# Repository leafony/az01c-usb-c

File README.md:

# Leafony AZ01C USB-C シリアル変換リーフ

## 概要

Leafony AZ01C は、Leafony Bus 向けの USB-C to UART リーフである。USB 接続時は FT234XD による USB-UART 変換と、USB VBUS から生成した 3.3V 電源を Leafony Bus へ供給する。

USB 未接続時に他リーフ側のバッテリーから 3.3V が供給される構成でも、UART 信号線と 3.3V 電源ラインのバックフィードを抑え、USB-C リーフ側が無駄な電力を消費しないことを設計方針とする。信号線は TS3A4741 で物理的に切断し、電源ラインは TPS6282533 出力と Leafony Bus 3.3V の間に MAX40200AUK+T 理想ダイオードを入れて逆流を遮断する。

## 主な用途

- Leafony リーフへの MCU 書き込み
- Leafony リーフの UART デバッグ
- USB から Leafony Bus への 3.3V 電源供給

## 仕様

### 電気的仕様

| 項目 | Min | Typ | Max | 単位 | 備考 |
|---|---:|---:|---:|---|---|
| USB VBUS 入力電圧 | 4.5 | 5.0 | 5.5 | V | USB-C UFP/Sink として使用 |
| Buck 出力電圧 `P3V3_BUCK` | 3.27 | 3.30 | 3.33 | V | TPS6282533 固定 3.3V、精度 ±1% |
| Leafony Bus 3.3V 出力 | - | 3.26 | - | V | MAX40200 通過後。500mA 時は約 43mV 低下 |
| Leafony Bus 3.3V 出力電流 | - | - | 500 | mA | TPS6282533 は 2A 品、MAX40200 は 1A 品。本設計では 500mA 上限 |
| MAX40200 逆方向リーク | - | 0.07 | 1.5 | µA | Leafony Bus +3.3V から `P3V3_BUCK` 方向 |
| UART 通信速度 | 300 | - | 3,000,000 | baud | FT234XD 仕様 |
| UART I/O 論理電圧 | - | 3.3 | - | V | FT234XD VCCIO を Leafony Bus 3.3V rail に接続 |
| USB 接続時アイドル消費 | - | 12 | - | mA | FT234XD、Buck、MAX40200、LED 周辺を含む概算 |
| USB 未接続時バッテリー側消費 | - | 0.15 | 2.3 | µA | MAX40200 逆方向リークと TS3A4741 待機電流のデータシート値から算出。FT234XD の VCC=0V、VCCIO=3.3V 条件は実機確認対象 |
| 動作温度範囲 | -40 | 25 | +85 | ℃ | 構成部品の最小共通範囲 |

### 機械的仕様

| 項目 | 仕様 |
|---|---|
| 外形寸法 | Leafony 20mm x 20mm |
| 基板厚 | 0.8mm 推奨 |
| 層数 | 4層 |
| 実装 | 両面実装 |
| USB コネクタ | Hirose CX90M-16P |
| 外部接続 | Leafony Bus 29ピン |

### USB 仕様

| 項目 | 仕様 |
|---|---|
| USB 規格 | USB 2.0 Full Speed (12Mbps) |
| コネクタ | USB Type-C |
| Type-C ロール | UFP / Sink Only |
| CC 抵抗 | CC1, CC2 それぞれ 5.1kΩ で GND へプルダウン |
| USB PD | 非対応 |
| ドライバ | FTDI VCP / D2XX |

## 回路設計

### 電源アーキテクチャ

```
USB VBUS 5V
  |
  +-- FB1 ---------------------> FT234XD.VCC
  |                                |
  |                                +--> FT234XD.3V3OUT
  |                                      |
  |                                      +--> TS3A4741.IN1/IN2
  |
  +----------------------------> TPS6282533.VIN
                                   |
                                   +-- EN = VIN
                                   |
                                   +-- SW -- L1 --> P3V3_BUCK
                                                   |
                                                   +--> MAX40200AUK+T
                                                        VDD = P3V3_BUCK
                                                        EN  = VDD
                                                        OUT = +3.3V rail
                                                              |
                                                              +--> FT234XD.VCCIO
                                                              +--> TS3A4741.V+
                                                              +--> LED1 pull-up
                                                              +--> Leafony Bus 3.3V (CN1 F1/B1)
```

`P3V3_BUCK` は TPS6282533 と MAX40200 の間のローカル電源レール、`+3.3V rail` は MAX40200 後段の Leafony Bus 側電源レールとする。

MAX40200 を入れることで、USB 未接続時に他リーフから Leafony Bus 3.3V が供給されても、`+3.3V rail -> P3V3_BUCK -> TPS6282533.SW/VIN -> VBUS` 方向の逆流を遮断する。MAX40200 の電圧降下により、Leafony Bus 側の実効電圧は TPS6282533 出力より低くなる。

### 動作状態

| 状態 | 電源 | UART 信号線 | 備考 |
|---|---|---|---|
| USB 接続、外部 3.3V なし | TPS6282533 から Leafony Bus へ 3.3V 供給 | TS3A4741 ON | 通常の USB-UART 動作 |
| USB 未接続、外部 3.3V なし | VBUS=0V、`P3V3_BUCK`=0V、Leafony Bus 3.3V=0V | TS3A4741 OFF | 基板側は実質停止 |
| USB 未接続、他リーフから 3.3V 供給 | Leafony Bus 3.3V は外部から印加。MAX40200 が Buck/VBUS 方向の逆流を遮断 | TS3A4741 OFF | FT234XD.3V3OUT=0V のためスイッチ制御は OFF |
| USB 接続、他リーフも 3.3V 供給 | 電源競合に注意 | TS3A4741 ON | 複数電源の同時接続を許容する場合はシステム側で電源 ORing 方針を確認 |

USB 未接続で他リーフから 3.3V が供給される場合、MAX40200 後段の `+3.3V rail` 配下である FT234XD.VCCIO、TS3A4741.V+、LED1 pull-up には電圧がかかる。一方で FT234XD.VCC は VBUS 由来のため 0V であり、FT234XD.3V3OUT も 0V となる。UART の TX/RX は TS3A4741 により切断される。

この状態でバッテリー側から USB-C リーフへ流れる消費電流は、データシート規定値からの見積もりで Typ 約 0.15µA、Max 約 2.3µA とする。内訳は MAX40200 の逆方向リーク Typ 0.07µA / Max 1.5µA と、TS3A4741 の VCC 待機電流 Typ 0.075µA / Max 0.75µA である。FT234XD は VCC=0V、VCCIO=3.3V の条件がデータシート上の通常動作条件ではないため、この見積もりには含めず、実機で USB 未接続時の Leafony Bus 3.3V 電流を確認する。

### バックフィード対策

バックフィード経路は大きく 2 つに分ける。

| 経路 | リスク | 対策 |
|---|---|---|
| UART TX/RX 信号線 | 他リーフ MCU の TX/RX が FT234XD の I/O 保護素子を通じて FT234XD 側を半端に給電する | TS3A4741 を TX/RX に直列挿入し、USB 未接続時は OFF |
| 3.3V 電源ライン | 他リーフの 3.3V が TPS6282533 の SW/L1 側から VIN/VBUS へ逆流する | MAX40200AUK+T を `P3V3_BUCK` と Leafony Bus 3.3V の間に直列挿入 |

TS3A4741 の IN1/IN2 は FT234XD.3V3OUT に接続する。USB 接続時は FT234XD が動作して 3V3OUT が High になり、TX/RX が接続される。USB 未接続時は 3V3OUT が 0V になり、TX/RX が物理的に切断される。

MAX40200 は VDD を `P3V3_BUCK`、OUT を Leafony Bus 3.3V、EN を VDD に接続する。USB 接続時は TPS6282533 から Leafony Bus へ給電し、USB 未接続時は Leafony Bus 3.3V から Buck/VBUS 側への逆流を遮断する。

### USB Type-C UFP 構成

| 信号 | 処理 |
|---|---|
| CC1, CC2 | 各々 5.1kΩ で GND へプルダウン |
| VBUS | A4, A9, B4, B9 をまとめて 5V 入力へ接続 |
| GND | A1, A12, B1, B12 を GND プレーンへ接続 |
| D+, D- | A面/B面の同名信号を基板上で接続し、FT234XD へ配線 |
| SBU1, SBU2 | NC |

USB PD には対応しない。CC 抵抗のみで USB Type-C の Sink/UFP として認識させる。

### ESD 保護

D+/D- ラインには USBLC6-2P6 を配置する。USB-C コネクタ近傍に置き、D+/D- へのスタブを短くする。VBUS は FB1 を通して基板内へ引き込む。必要に応じて、VBUS 用 TVS ダイオードの追加余地を検討する。

### 通信インジケータ LED

FT234XD の CBUS0 を FT_PROG で `TX&RXLED#` に設定し、LED1 を TX/RX 共用インジケータとして使用する。

## Leafony Bus ピンアサイン

| ピン名 | F面 / B面 | 信号 | 用途 |
|---|---|---|---|
| 3.3V | F1 / B1 | +3.3V rail | MAX40200 通過後の 3.3V 電源。USB から他リーフへ最大 500mA 供給 |
| VBUS | F3 / B3 | VBUS 5V | USB VBUS。必要な他リーフで参照可能 |
| D0 | F18 / B18 | UART TX | FT234XD TXD から他リーフ MCU RX へ。TS3A4741 Ch1 経由 |
| D1 | F20 / B20 | UART RX | 他リーフ MCU TX から FT234XD RXD へ。TS3A4741 Ch2 経由 |
| GND | F27 / B27 | GND | 共通グラウンド |

## 主要部品

| Ref | 型番 | 役割 |
|---|---|---|
| U1 | TS3A4741DCNR | UART TX/RX 切断用 2ch SPST アナログスイッチ |
| U2 | USBLC6-2P6 | USB D+/D- ESD 保護 |
| U3 | FT234XD | USB-UART ブリッジ |
| U4 | TPS6282533DMQR | 5V から 3.3V を生成する Buck コンバータ |
| U5 | MAX40200AUK+T | 3.3V 電源ライン逆流防止用 ideal diode |
| J1 | CX90M-16P | USB Type-C レセプタクル |
| L1 | 0.47uH | TPS6282533 用インダクタ |
| FB1 | 600Ω @ 100MHz | VBUS 入力ノイズ抑制 |

## ソフトウェア

### ドライバ

FTDI 公式の VCP または D2XX ドライバを使用する。

| OS | ドライバ | 備考 |
|---|---|---|
| Windows 10/11 | 標準ドライバ自動インストール | 必要に応じて FTDI 公式ドライバを使用 |
| macOS | 標準 Apple FTDI ドライバ | macOS 10.9 以降 |
| Linux | `ftdi_sio` | 多くのディストリビューションで自動認識 |

### 初期設定 (FT_PROG)

量産前に FT234XD 内蔵 MTP へ以下を設定する。

| パラメータ | 設定値 | 備考 |
|---|---|---|
| CBUS0 Function | `TX&RXLED#` | LED1 通信インジケータ用 |
| Manufacturer Name | 任意 | 例: `mitdir` |
| Product Description | 任意 | 例: `Leafony USB-UART Bridge` |
| Serial Number | ユニーク値 | 複数台接続時の識別用 |
| USB Vendor ID | `0x0403` | FTDI デフォルト |
| USB Product ID | `0x6015` | FT-X デフォルト |

## 設計反映メモ

この README は、MAX40200AUK+T を追加した電源構成を前提とする。KiCad 回路図、PCB、BOM を更新する場合は、少なくとも以下を反映する。

- `U5: MAX40200AUK+T` を追加する
- TPS6282533 の出力側を `P3V3_BUCK` とし、Leafony Bus 側 `+3.3V rail` と分離する
- MAX40200 の VDD を `P3V3_BUCK`、OUT を `+3.3V rail`、EN を VDD に接続する
- Leafony Bus 3.3V、FT234XD.VCCIO、TS3A4741.V+、LED1 pull-up は MAX40200 後段の `+3.3V rail` に接続する
- BOM に MAX40200AUK+T と対応フットプリントを追加する

あわせて以下を実機またはデータシートで確認する。

- USB 未接続かつ他リーフから 3.3V が供給される状態で、FT234XD.VCC=0V、FT234XD.VCCIO=3.3V となることを許容できるか
- USB 接続中に他リーフ側の 3.3V 電源も同時に有効になるシステム構成を許容するか
- MAX40200 の電圧降下込みで、Leafony Bus 側 3.3V rail の最小電圧が接続先リーフの要求を満たすか

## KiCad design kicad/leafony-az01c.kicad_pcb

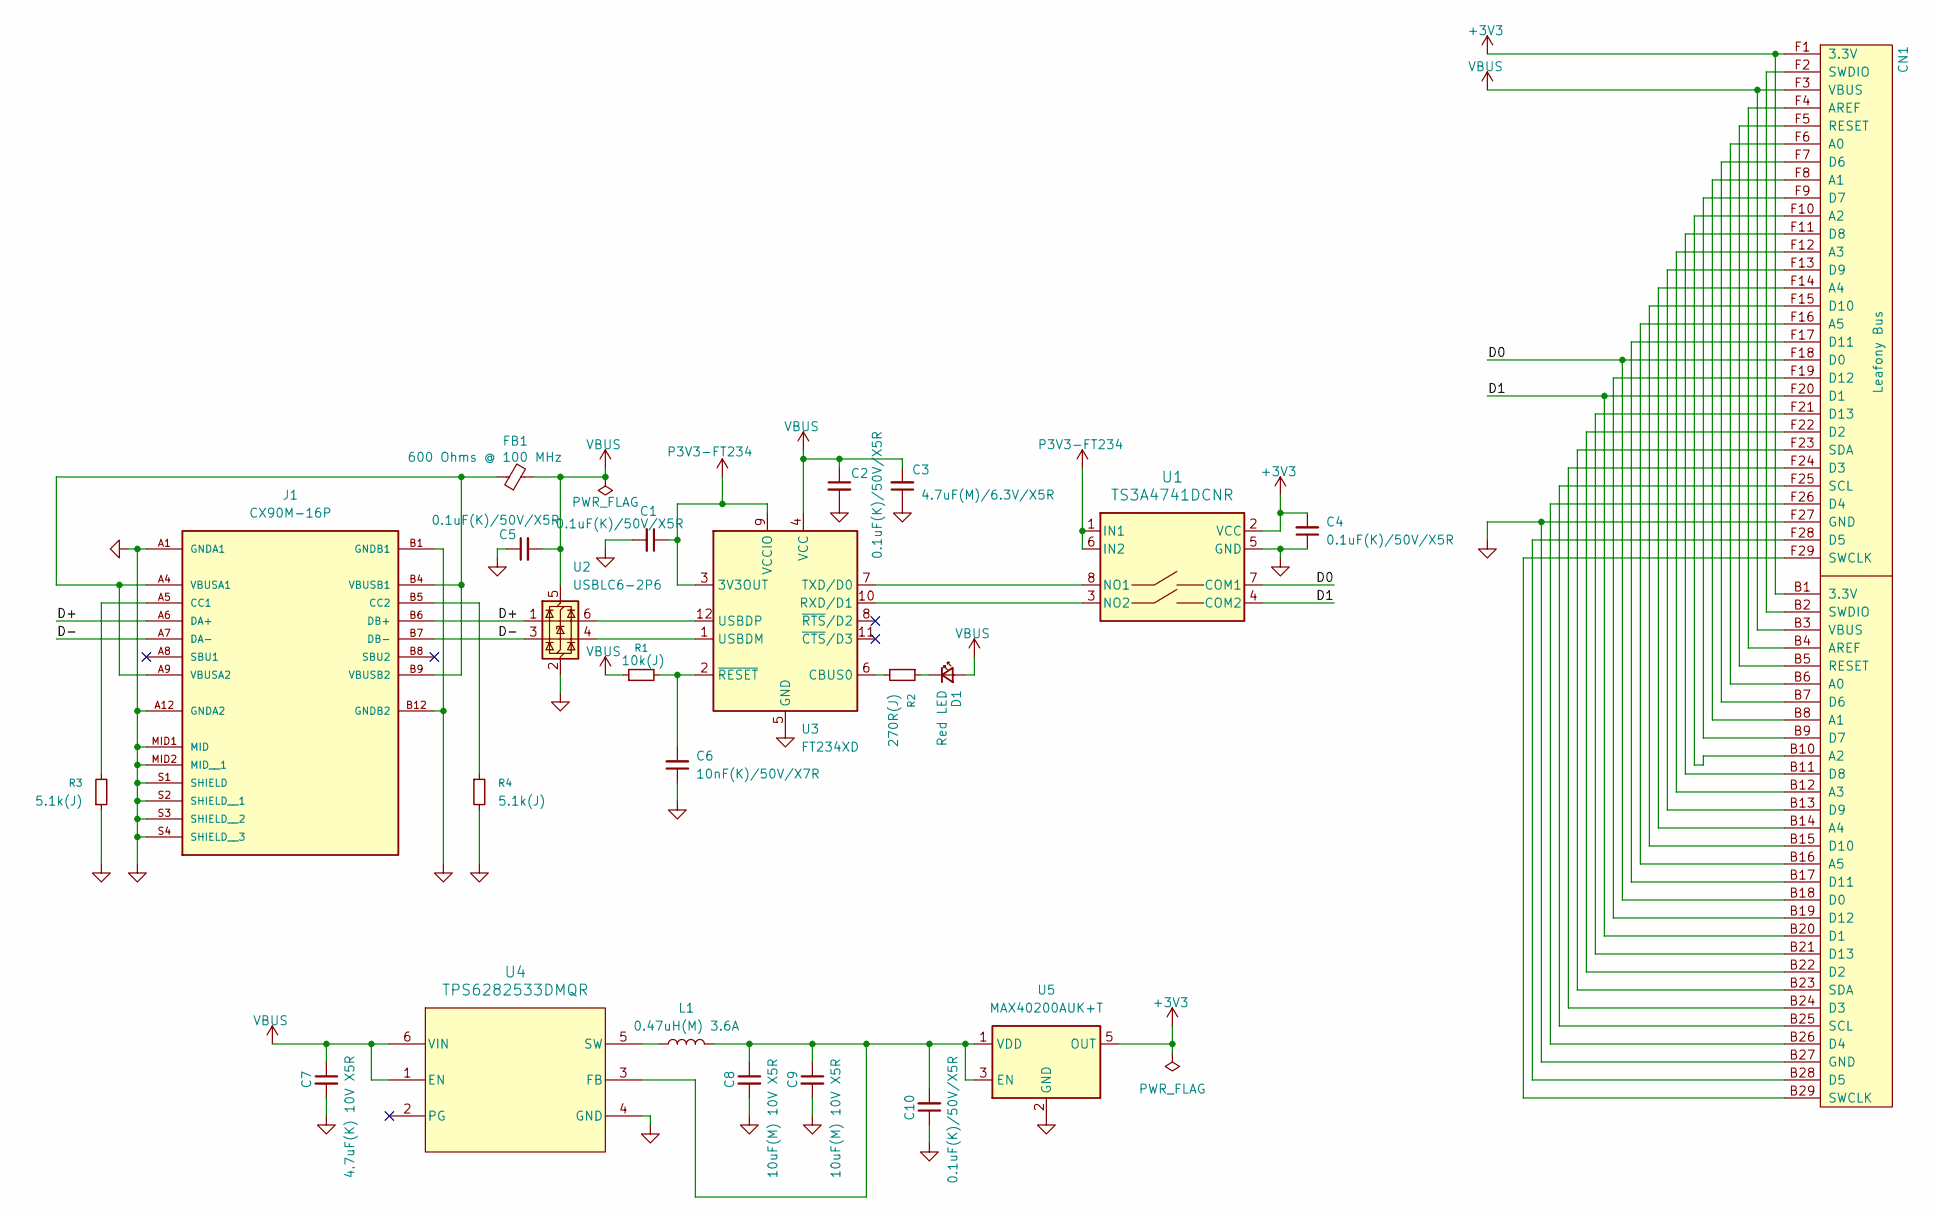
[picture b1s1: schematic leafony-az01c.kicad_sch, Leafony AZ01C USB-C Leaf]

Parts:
C1, C2, C4, C5, C10: 0.1uF(K)/50V/X5R; C_0402_1005Metric; MPN CC0402KRX5R9BB104
C3: 4.7uF(M)/6.3V/X5R; C_0402_1005Metric; MPN CC0402MRX5R5BB475
C6: 10nF(K)/50V/X7R; C_0402_1005Metric; MPN CC0402KRX7R9BB103
C7: 4.7uF(K) 10V X5R; C_0603_1608Metric; MPN CC0603KRX5R6BB475
C8, C9: 10uF(M) 10V X5R; C_0603_1608Metric; MPN CC0603MRX5R6BB106
CN1: Leafony Bus; CN_F29_B29
D1: Red LED; LED_0603_1608Metric; MPN SML-D14VWT86AAS
FB1: 600 Ohms @ 100 MHz; L_0805_2012Metric; MPN MI0805K601R-10
J1: CX90M-16P; HRS_CX90M-16P; PARTREV 2
L1: 0.47uH(M) 3.6A; L_Murata_DFE201610P; MPN DFE201610E-R47M=P2
R1: 10k(J); R_0402_1005Metric; MPN RC0402JR-0710KL
R2: 270R(J); R_0402_1005Metric; MPN RC0402JR-07270RL
R3, R4: 5.1k(J); R_0402_1005Metric; MPN RC0402JR-075K1L
U1: TS3A4741DCNR; SOT-23-8; MPN TS3A4741DCNR
U2: USBLC6-2P6; SOT-666; MPN USBLC6-2P6
U3: FT234XD; WDFN-12-1EP_3x3mm_P0.45mm_EP1.7x2.5mm; MPN FT234XD-T
U4: TPS6282533DMQR; DMQ0006A; MPN TPS6282533DMQR
U5: MAX40200AUK+T; SOT-23-5; MPN MAX40200AUK+T

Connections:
+3V3: C4.2, CN1.B1 (3.3V), CN1.F1 (3.3V), U1.2 (VCC), U5.5 (OUT)
/D0: CN1.B18 (D0), CN1.F18 (D0), U1.7 (COM1)
/D1: CN1.B20 (D1), CN1.F20 (D1), U1.4 (COM2)
/D+: J1.A6 (DA+), J1.B6 (DB+), U2.1 (I/O1)
/D-: J1.A7 (DA-), J1.B7 (DB-), U2.3 (I/O2)
GND: C1.2, C2.2, C3.1, C4.1, C5.1, C6.1, C7.2, C8.2, C9.2, C10.1, CN1.B27 (GND), CN1.F27 (GND), J1.A1 (GNDA1), J1.A12 (GNDA2), J1.B1 (GNDB1), J1.B12 (GNDB2), J1.MID1 (MID), J1.MID2 (MID__1), J1.S1 (SHIELD), J1.S2 (SHIELD__1), J1.S3 (SHIELD__2), J1.S4 (SHIELD__3), R3.1, R4.2, U1.5 (GND), U2.2 (GND), U3.5 (GND), U3.13 (GND), U4.4 (GND), U5.2 (GND)
unnamed: CN1.B6 (A0), CN1.F6 (A0)
unnamed: CN1.B8 (A1), CN1.F8 (A1)
unnamed: CN1.B10 (A2), CN1.F10 (A2)
unnamed: CN1.B12 (A3), CN1.F12 (A3)
unnamed: CN1.B14 (A4), CN1.F14 (A4)
unnamed: CN1.B16 (A5), CN1.F16 (A5)
unnamed: CN1.B4 (AREF), CN1.F4 (AREF)
unnamed: CN1.B22 (D2), CN1.F22 (D2)
unnamed: CN1.B24 (D3), CN1.F24 (D3)
unnamed: CN1.B26 (D4), CN1.F26 (D4)
unnamed: CN1.B28 (D5), CN1.F28 (D5)
unnamed: CN1.B7 (D6), CN1.F7 (D6)
unnamed: CN1.B9 (D7), CN1.F9 (D7)
unnamed: CN1.B11 (D8), CN1.F11 (D8)
unnamed: CN1.B13 (D9), CN1.F13 (D9)
unnamed: CN1.B15 (D10), CN1.F15 (D10)
unnamed: CN1.B17 (D11), CN1.F17 (D11)
unnamed: CN1.B19 (D12), CN1.F19 (D12)
unnamed: CN1.B21 (D13), CN1.F21 (D13)
unnamed: CN1.B5 (RESET), CN1.F5 (RESET)
unnamed: CN1.B25 (SCL), CN1.F25 (SCL)
unnamed: CN1.B23 (SDA), CN1.F23 (SDA)
unnamed: CN1.B29 (SWCLK), CN1.F29 (SWCLK)
unnamed: CN1.B2 (SWDIO), CN1.F2 (SWDIO)
unnamed: D1.1 (K), R2.1
unnamed: J1.A5 (CC1), R3.2
unnamed: J1.B5 (CC2), R4.1
unnamed: FB1.1, J1.A4 (VBUSA1), J1.A9 (VBUSA2), J1.B4 (VBUSB1), J1.B9 (VBUSB2)
unnamed: U1.8 (NO1), U3.7 (TXD/D0)
unnamed: U1.3 (NO2), U3.10 (RXD/D1)
unnamed: R2.2, U3.6 (CBUS0)
unnamed: U2.4 (I/O2), U3.1 (USBDM)
unnamed: U2.6 (I/O1), U3.12 (USBDP)
unnamed: C6.2, R1.2, U3.2 (~RESET)
unnamed: C8.1, C9.1, C10.2, L1.2, U4.3 (FB), U5.1 (VDD), U5.3 (EN)
unnamed: L1.1, U4.5 (SW)
P3V3-FT234: C1.1, U1.1 (IN1), U1.6 (IN2), U3.3 (3V3OUT), U3.9 (VCCIO)
VBUS: C2.1, C3.2, C5.2, C7.1, CN1.B3 (VBUS), CN1.F3 (VBUS), D1.2 (A), FB1.2, R1.1, U2.5 (VBUS), U3.4 (VCC), U4.1 (EN), U4.6 (VIN)

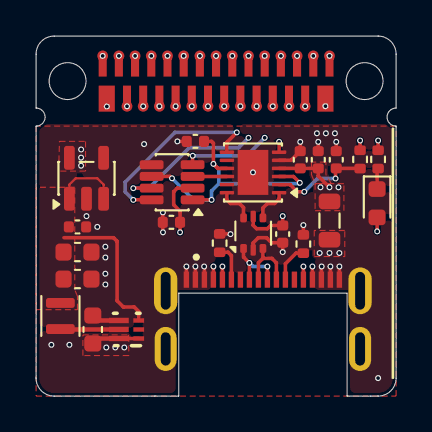
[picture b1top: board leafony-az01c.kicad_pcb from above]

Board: 4 copper layers, 20.0 x 20.0 mm, 24 parts (0 on the bottom side), 44 nets.

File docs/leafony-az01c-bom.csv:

"Reference","Value","Datasheet","Footprint","Qty","DNP","MANUFACTURER","MPN"
"C1,C2,C4,C5,C10","0.1uF(K)/50V/X5R","https://yageogroup.com/content/datasheet/asset/file/UPY-GPHC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","Capacitor_SMD:C_0402_1005Metric","5","","YAGEO","CC0402KRX5R9BB104"
"C3","4.7uF(M)/6.3V/X5R","https://yageogroup.com/content/datasheet/asset/file/UPY-GPHC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","Capacitor_SMD:C_0402_1005Metric","1","","YAGEO","CC0402MRX5R5BB475"
"C6","10nF(K)/50V/X7R","https://yageogroup.com/content/datasheet/asset/file/UPY-GPHC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","Capacitor_SMD:C_0402_1005Metric","1","","YAGEO","CC0402KRX7R9BB103"
"C7","4.7uF(K) 10V X5R","https://yageogroup.com/content/datasheet/asset/file/UPY-GPHC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","Capacitor_SMD:C_0603_1608Metric","1","","YAGEO","CC0603KRX5R6BB475"
"C8,C9","10uF(M) 10V X5R","https://yageogroup.com/content/datasheet/asset/file/UPY-GPHC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","Capacitor_SMD:C_0603_1608Metric","2","","YAGEO","CC0603MRX5R6BB106"
"D1","Red LED","https://www.rohm.com/products/led/chip-leds-mono-color-type/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","LED_SMD:LED_0603_1608Metric","1","","ROHM","SML-D14VWT86AAS"
"FB1","600 Ohms @ 100 MHz","https://www.laird.com/document/datasheet/mi0805k601r-10-datasheet","Inductor_SMD:L_0805_2012Metric","1","","Laird","MI0805K601R-10"
"J1","CX90M-16P","https://www.hirose.com/product/document?clcode=CL0480-0522-0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","Leafony:HRS_CX90M-16P","1","","Hirose","CX90M-16P"
"L1","0.47uH(M) 3.6A","https://search.murata.co.jp/Ceramy/image/img/P02/J(E)TE243A-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","Inductor_SMD:L_Murata_DFE201610P","1","","Murata Electronics","DFE201610E-R47M=P2"
"R1","10k(J)","https://yageogroup.com/content/datasheet/asset/file/PYU-RC_G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","Resistor_SMD:R_0402_1005Metric","1","","YAGEO","RC0402JR-0710KL"
"R2","270R(J)","https://yageogroup.com/content/datasheet/asset/file/PYU-RC_G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","Resistor_SMD:R_0402_1005Metric","1","","YAGEO","RC0402JR-07270RL"
"R3,R4","5.1k(J)","https://yageogroup.com/content/datasheet/asset/file/PYU-RC_G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","Resistor_SMD:R_0402_1005Metric","2","","YAGEO","RC0402JR-075K1L"
"U1","TS3A4741DCNR","https://www.ti.com/lit/gpn/ts3a4741","Package_TO_SOT_SMD:SOT-23-8","1","","Texas Instruments","TS3A4741DCNR"
"U2","USBLC6-2P6","https://www.st.com/resource/en/datasheet/usblc6-2.pdf","Package_TO_SOT_SMD:SOT-666","1","","STMicroelectronics","USBLC6-2P6"
"U3","FT234XD","https://ftdichip.com/wp-content/uploads/2024/05/DS_FT234XD.pdf","Package_DFN_QFN:WDFN-12-1EP_3x3mm_P0.45mm_EP1.7x2.5mm","1","","FTDI","FT234XD-T"
"U4","TPS6282533DMQR","https://www.ti.com/lit/gpn/tps62825","Leafony:DMQ0006A","1","","Texas Instruments","TPS6282533DMQR"
"U5","MAX40200AUK+T","https://datasheets.maximintegrated.com/en/ds/MAX40200.pdf","Package_TO_SOT_SMD:SOT-23-5","1","","Analog Devices Inc./Maxim Integrated","MAX40200AUK+T"

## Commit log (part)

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2026-04-26 ディレクトリを整理
2026-04-26 BOMを出力
2026-04-26 ガーバーを出力
2026-05-11 BOM修正
2026-05-22 面付基板を更新
2026-05-22 kicad 10
2026-05-22 MAX40200AUK+Tに関する記述を追加
2026-05-22 README.mdの内容を更新し、MAX40200AUK+Tを追加した電源構成に関する詳細を反映
2026-05-22 BOMとガーバーを更新
2026-05-23 回路図とレイアウトを更新
2026-06-29 README.mdの内容を更新し、USB未接続時の消費電流に関する詳細を追加
